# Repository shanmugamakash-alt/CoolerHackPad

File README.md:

# CoolerHackPad

CoolerHackPad is a 6-key Hackpad designed as a DIY alternative to a Stream Deck rather than a standard keyboard. VIA support is planned for a future update to make it a fully customizable macro pad.

---

## Features

* **Switches:** 6x Cherry MX-compatible key switches
* **Firmware:** QMK support (VIA support coming soon)
* **Enclosure:** 2-piece case (Top cover and Base)
* **Design:** Custom ventilation cutouts and styled USB port opening

---

## 3D Model

The case was modeled in **Fusion 360** and consists of two parts:
* **Base:** Holds the PCB, switches, and microcontroller. Fits together using M3 screws threaded directly into the plastic.
* **Top Cover:** Features cutouts for the key switches and ventilation holes for the PCB.

*Note: Parts of the case will be painted white to match the intended design aesthetic.*

---

## PCB

### Schematics

### PCB Design

Designed in **KiCad**.

---

## Development Notes

This project was built entirely from scratch. AI assistance was used for software navigation and documentation reference—specifically for locating tools in KiCad and Fusion 360 (e.g., finding the move tool in Fusion 360, creating edge cutouts in KiCad) and formatting the QMK `keymap.c` firmware file. All hardware designs, 3D models, and code implementation were created independently.

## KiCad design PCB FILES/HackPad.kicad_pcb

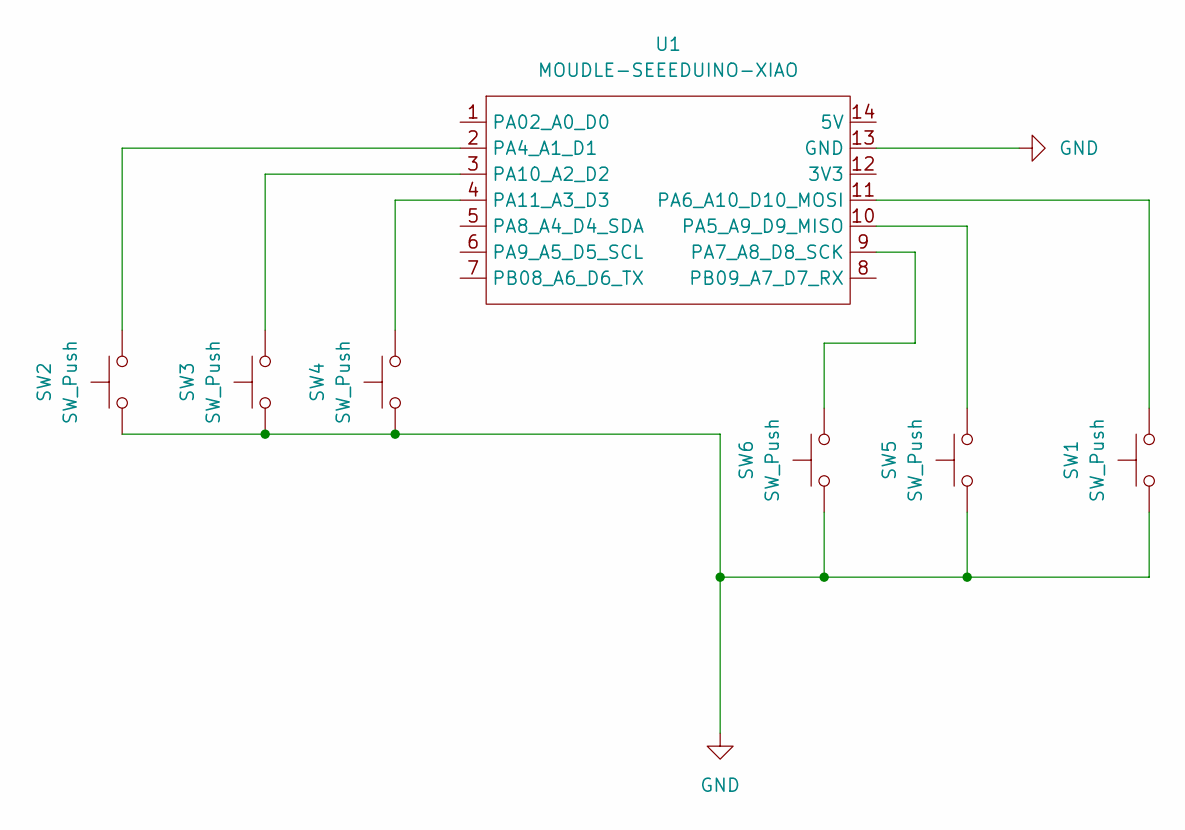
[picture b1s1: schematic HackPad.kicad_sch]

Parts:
SW1, SW2, SW3, SW4, SW5, SW6: SW_Push; SW_Cherry_MX_1.00u_PCB
U1: MOUDLE-SEEEDUINO-XIAO; XIAO-Generic-Hybrid-14P-2.54-21X17.8MM

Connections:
GND: SW1.1, SW2.1, SW3.1, SW4.1, SW5.1, SW6.1, U1.13 (GND)
unnamed: SW2.2, U1.2 (PA4_A1_D1)
unnamed: SW5.2, U1.10 (PA5_A9_D9_MISO)
unnamed: SW1.2, U1.11 (PA6_A10_D10_MOSI)
unnamed: SW6.2, U1.9 (PA7_A8_D8_SCK)
unnamed: SW3.2, U1.3 (PA10_A2_D2)
unnamed: SW4.2, U1.4 (PA11_A3_D3)

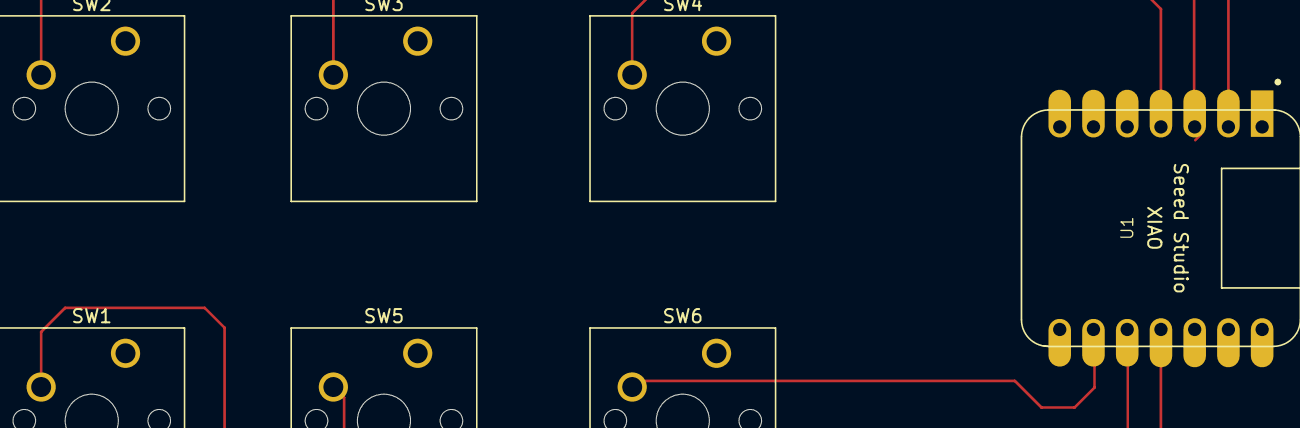
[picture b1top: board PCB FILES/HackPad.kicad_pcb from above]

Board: 2 copper layers, 7 parts (0 on the bottom side), 7 nets.

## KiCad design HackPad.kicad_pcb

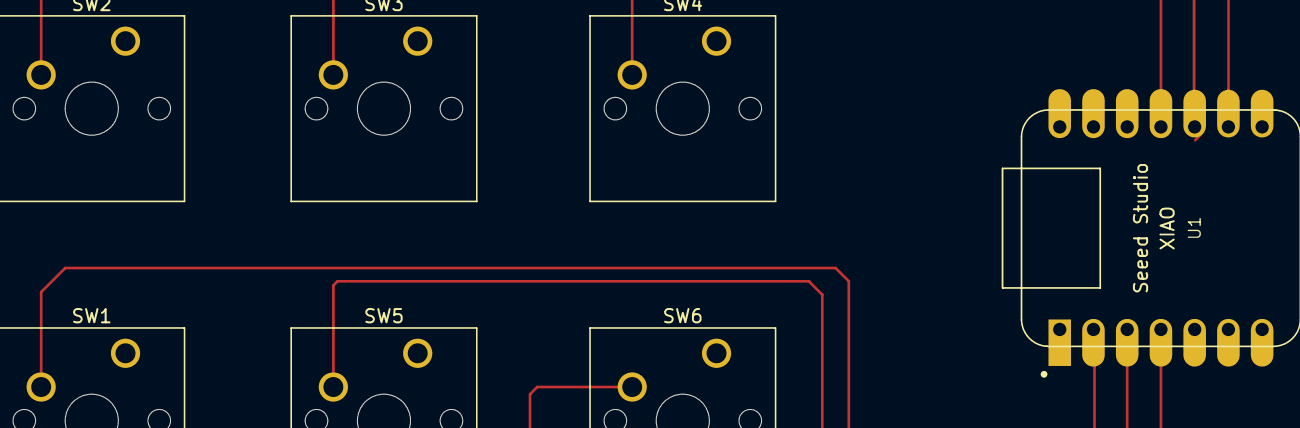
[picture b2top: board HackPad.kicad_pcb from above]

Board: 2 copper layers, 7 parts (0 on the bottom side), 7 nets.

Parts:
SW1, SW2, SW3, SW4, SW5, SW6: SW_Push; SW_Cherry_MX_1.00u_PCB
U1: MOUDLE-SEEEDUINO-XIAO; XIAO-Generic-Hybrid-14P-2.54-21X17.8MM

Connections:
GND: SW1.1, SW2.1, SW3.1, SW4.1, SW5.1, SW6.1, U1.13 (GND)
unnamed: SW1.2, U1.2 (PA4_A1_D1)
unnamed: SW3.2, U1.10 (PA5_A9_D9_MISO)
unnamed: SW4.2, U1.11 (PA6_A10_D10_MOSI)
unnamed: SW2.2, U1.9 (PA7_A8_D8_SCK)
unnamed: SW5.2, U1.3 (PA10_A2_D2)
unnamed: SW6.2, U1.4 (PA11_A3_D3)
